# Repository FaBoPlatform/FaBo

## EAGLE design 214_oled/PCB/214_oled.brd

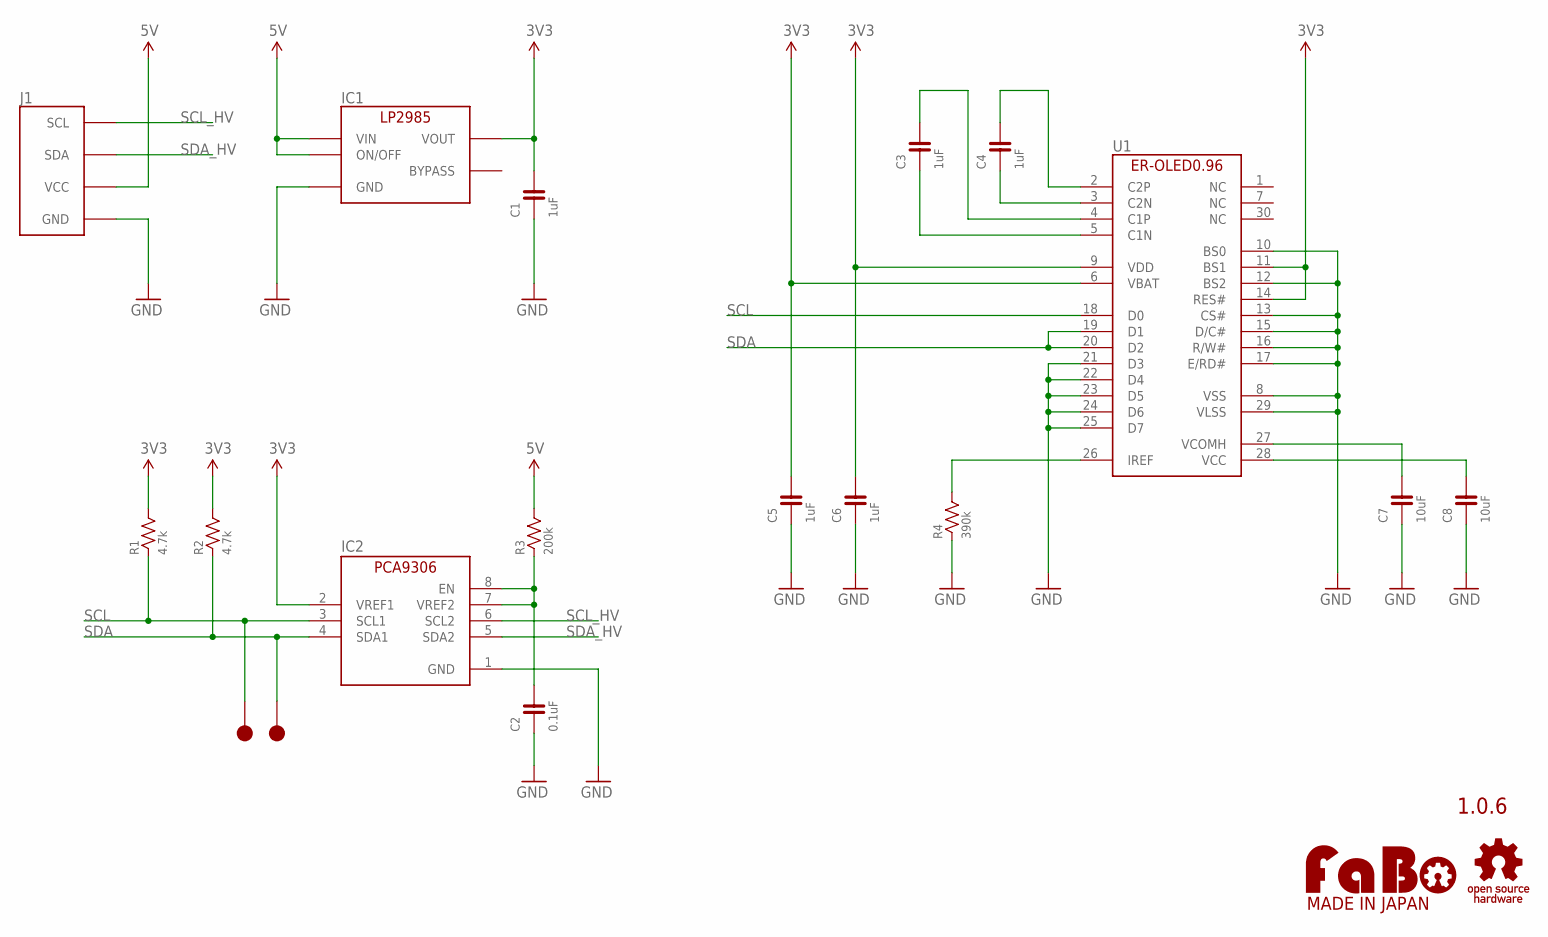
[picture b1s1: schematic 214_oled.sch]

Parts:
C1, C3, C4, C5, C6: 1uF; 0603
C2: 0.1uF; 0603
C7, C8: 10uF; 0603
IC1: LP2985-33DBV; SOT-23-5
IC2: PCA9306GM; XQFN8
J1: FABO_BRICK_I2C-OLED; FABO_BRICK_I2C_OLED
R1, R2: 4.7k; 0603
R3: 200k; 0603
R4: 390k; 0603
TP1, TP2: TP-15
U1: ER-OLED0.96-1
U$2: LOGO_OSHW-M; LOGO_OSHW_M
U$3: LOGO_FABO-M_BOTTOM; LOGO_FABO_MS_BOTTOM

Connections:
3V3: C1.2, C5.2, C6.2, IC1.5 (VOUT), IC2.2 (VREF1), R1.2, R2.2, U1.6 (VBAT), U1.9 (VDD), U1.11 (BS1), U1.14 (RES#)
5V: IC1.1 (VIN), IC1.3 (ON/OFF), J1.VCC, R3.2
GND: C1.1, C2.1, C5.1, C6.1, C7.1, C8.1, IC1.2 (GND), IC2.1 (GND), J1.GND, R4.1, U1.8 (VSS), U1.10 (BS0), U1.12 (BS2), U1.13 (CS#), U1.15 (D/C#), U1.16 (R/W#), U1.17 (E/RD#), U1.21 (D3), U1.22 (D4), U1.23 (D5), U1.24 (D6), U1.25 (D7), U1.29 (VLSS)
unnamed: C3.2, U1.4 (C1P)
unnamed: C3.1, U1.5 (C1N)
unnamed: C4.1, U1.3 (C2N)
unnamed: C4.2, U1.2 (C2P)
unnamed: R4.2, U1.26 (IREF)
unnamed: C7.2, U1.27 (VCOMH)
unnamed: C8.2, U1.28 (VCC)
unnamed: C2.2, IC2.7 (VREF2), IC2.8 (EN), R3.1
SCL: IC2.3 (SCL1), R1.1, TP2.1, U1.18 (D0)
SCL_HV: IC2.6 (SCL2), J1.SCL
SDA: IC2.4 (SDA1), R2.1, TP1.1, U1.19 (D1), U1.20 (D2)
SDA_HV: IC2.5 (SDA2), J1.SDA

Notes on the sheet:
1.0.6

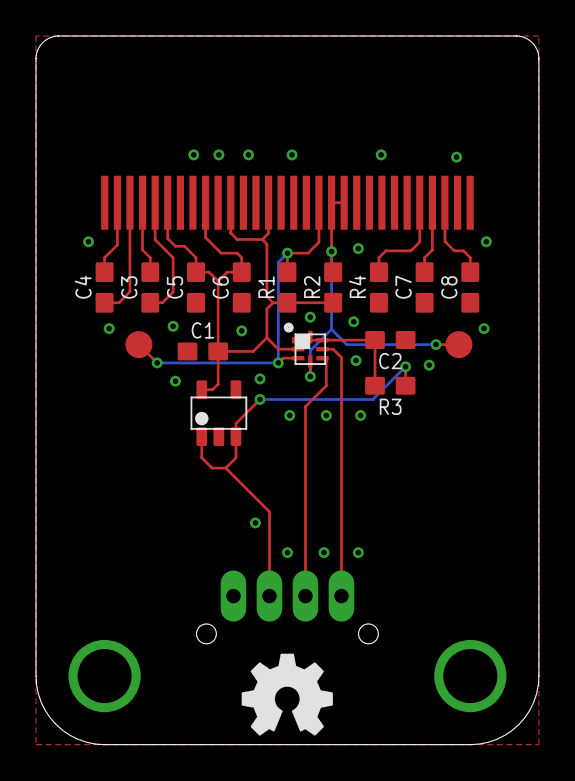
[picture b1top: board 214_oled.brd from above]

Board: 2 copper layers, 27.9 x 39.4 mm, 20 parts (1 on the bottom side), 15 nets.

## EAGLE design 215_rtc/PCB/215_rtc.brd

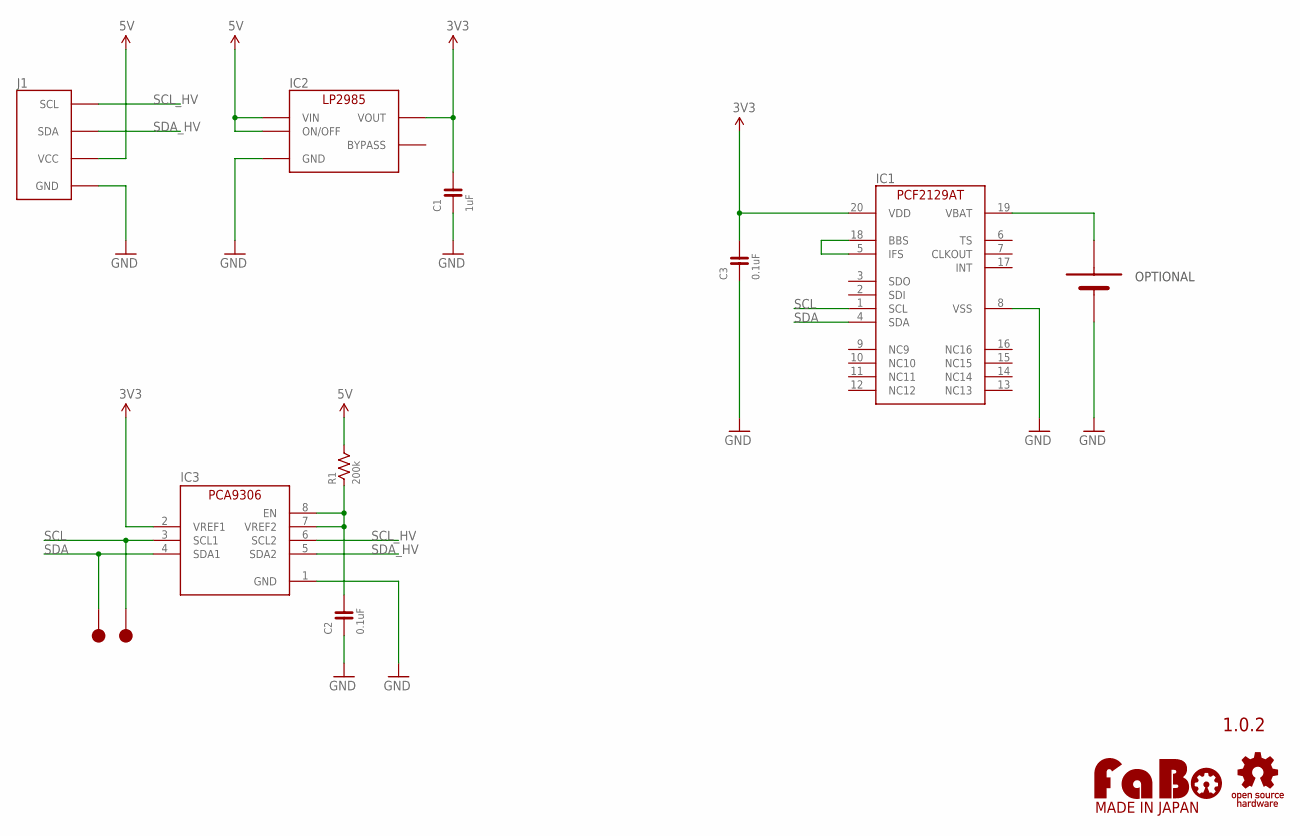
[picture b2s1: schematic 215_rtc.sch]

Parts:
C1: 1uF; 0603
C2, C3: 0.1uF; 0603
IC1: RTC-PCF2129AT; SO20
IC2: TI-LP2985-33DBVR; TI-LP2985
IC3: PCA9306DQER; X2SON
J1: FABO_BRICK_I2C
R1: 200k; 0603
TP1, TP2: TP-10
U$2: LOGO_OSHW-M_BOTTOM; LOGO_OSHW_M_BOTTOM
U$3: LOGO_FABO-M; LOGO_FABO_MS
U$4: BATTERY-SMTU2450; TAKACHI-SMTU2450

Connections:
3V3: C1.2, C3.2, IC1.20 (VDD), IC2.5 (VOUT), IC3.2 (VREF1)
5V: IC2.1 (VIN), IC2.3 (ON/OFF), J1.VCC, R1.2
GND: C1.1, C2.1, C3.1, IC1.8 (VSS), IC2.2 (GND), IC3.1 (GND), J1.GND, U$4.2 (-)
unnamed: IC1.19 (VBAT), U$4.1 (+)
unnamed: C2.2, IC3.7 (VREF2), IC3.8 (EN), R1.1
unnamed: IC1.5 (IFS), IC1.18 (BBS)
SCL: IC1.1 (SCL), IC3.3 (SCL1), TP2.1
SCL_HV: IC3.6 (SCL2), J1.SCL
SDA: IC1.4 (SDA), IC3.4 (SDA1), TP1.1
SDA_HV: IC3.5 (SDA2), J1.SDA

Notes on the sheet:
1.0.2
OPTIONAL

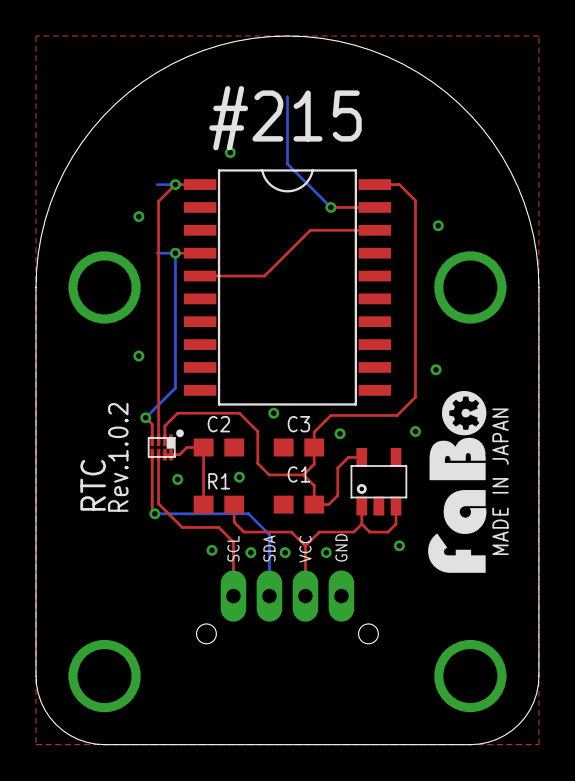
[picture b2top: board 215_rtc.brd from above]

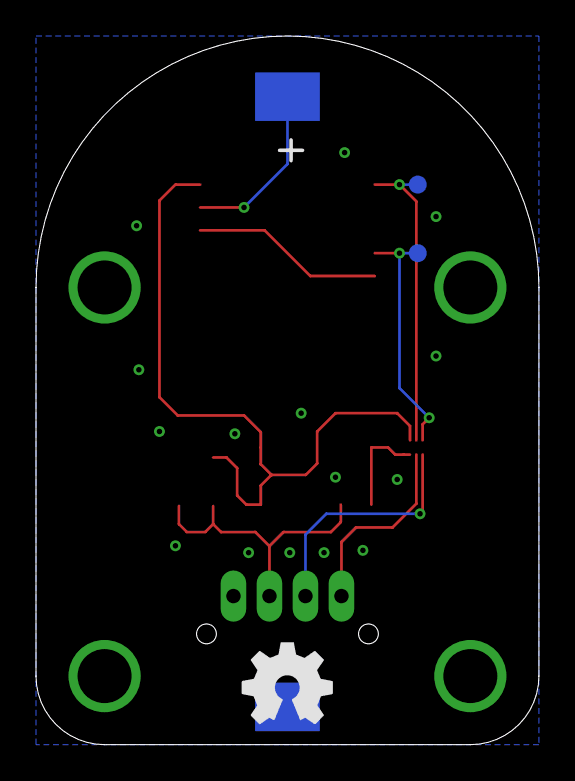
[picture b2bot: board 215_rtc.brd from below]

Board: 2 copper layers, 27.9 x 39.4 mm, 13 parts (3 on the bottom side), 10 nets.

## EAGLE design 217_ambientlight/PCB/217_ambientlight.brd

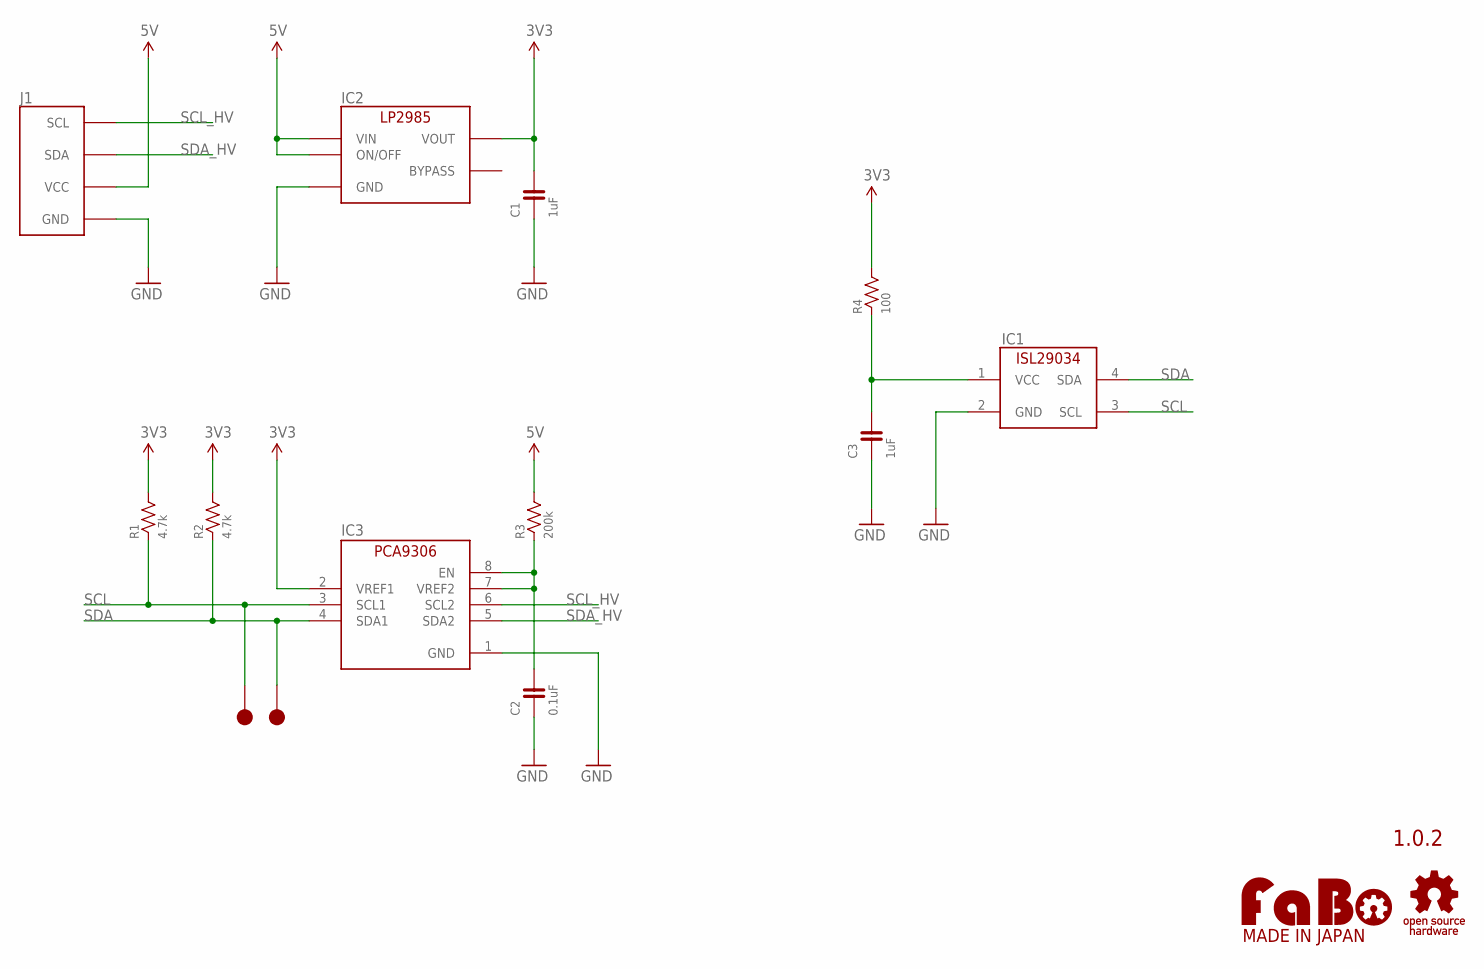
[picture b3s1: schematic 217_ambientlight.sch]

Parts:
C1, C3: 1uF; 0603
C2: 0.1uF; 0603
IC1: IN-ISL29034; INTERSIL-ISL29034
IC2: LP2985-33DBV; SOT-23-5
IC3: PCA9306GM; XQFN8
J1: FABO_BRICK_I2C
R1, R2: 4.7k; 0603
R3: 200k; 0603
R4: 100; 0603
TP1, TP2: TP-15
U$2: LOGO_OSHW-M_BOTTOM; LOGO_OSHW_M_BOTTOM
U$3: LOGO_FABO-M; LOGO_FABO_MS

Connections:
3V3: C1.2, IC2.5 (VOUT), IC3.2 (VREF1), R1.2, R2.2, R4.2
5V: IC2.1 (VIN), IC2.3 (ON/OFF), J1.VCC, R3.2
GND: C1.1, C2.1, C3.1, IC1.2 (GND), IC2.2 (GND), IC3.1 (GND), J1.GND
unnamed: C2.2, IC3.7 (VREF2), IC3.8 (EN), R3.1
SCL: IC1.3 (SCL), IC3.3 (SCL1), R1.1, TP2.1
SCL_HV: IC3.6 (SCL2), J1.SCL
SDA: IC1.4 (SDA), IC3.4 (SDA1), R2.1, TP1.1
SDA_HV: IC3.5 (SDA2), J1.SDA
VCC: C3.2, IC1.1 (VCC), R4.1

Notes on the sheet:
1.0.2

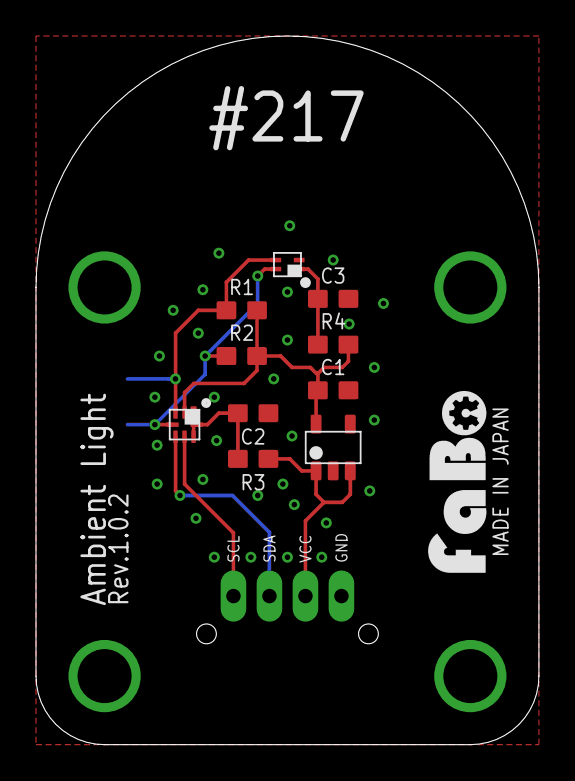
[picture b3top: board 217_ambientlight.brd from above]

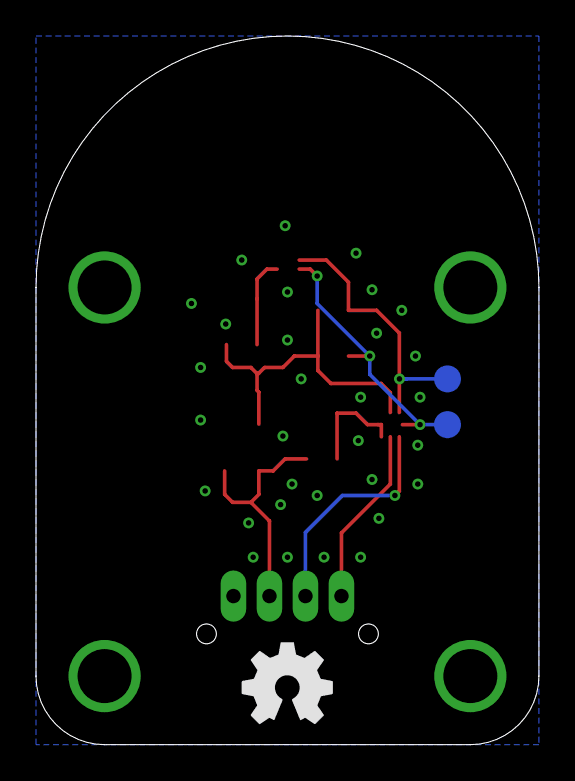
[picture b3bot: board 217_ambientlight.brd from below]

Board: 2 copper layers, 27.9 x 39.4 mm, 15 parts (2 on the bottom side), 9 nets.

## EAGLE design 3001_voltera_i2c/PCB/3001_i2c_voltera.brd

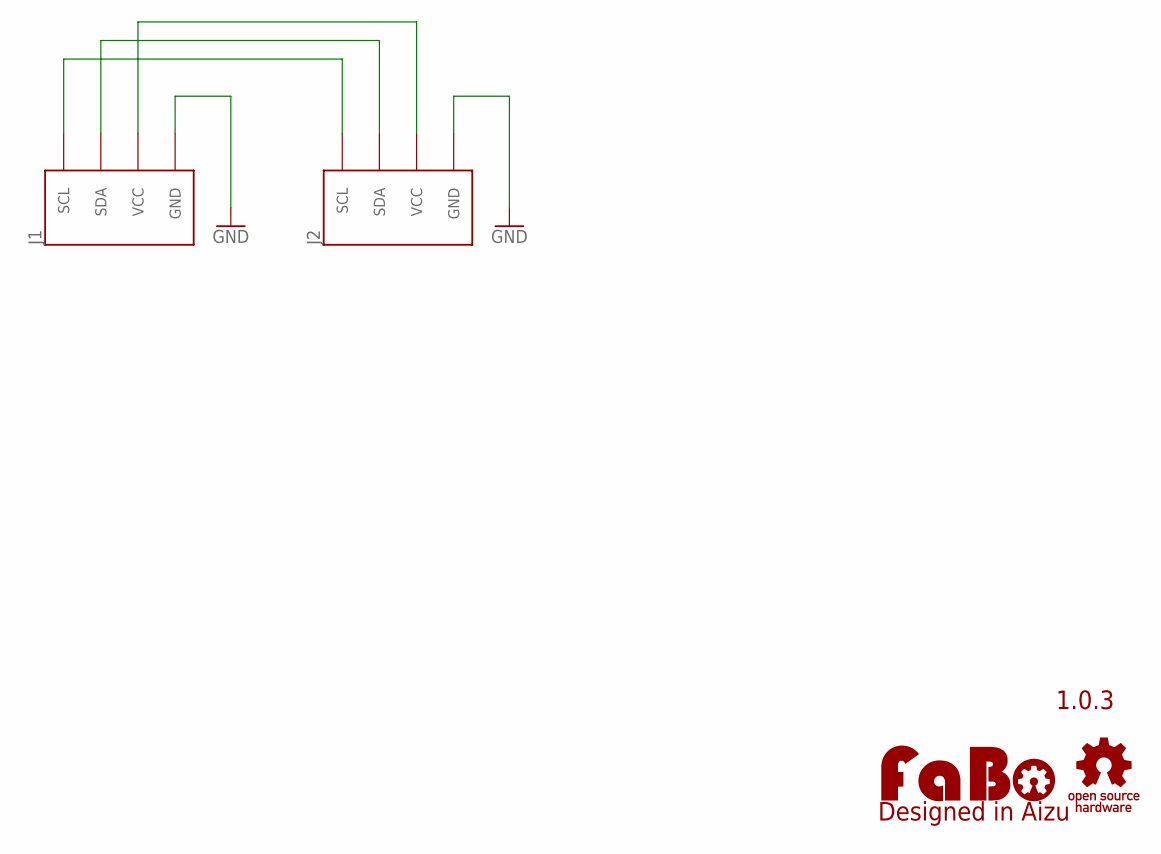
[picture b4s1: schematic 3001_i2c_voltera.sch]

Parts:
J1: FABO_BRICK_I2C-VOLTERA-BASE; FABO_BRICK_I2C_VOLTERA_BASE
J2: FABO_BRICK_I2C-VOLTERA-PAD; FABO_BRICK_I2C_VOLTERA_PAD
U$2: LOGO_OSHW-M_BOTTOM; LOGO_OSHW_M_BOTTOM
U$3: LOGO_FABO-S; LOGO_FABO_S

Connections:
GND: J1.GND, J2.GND
unnamed: J1.SCL, J2.SCL
unnamed: J1.SDA, J2.SDA
unnamed: J1.VCC, J2.VCC

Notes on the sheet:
1.0.3

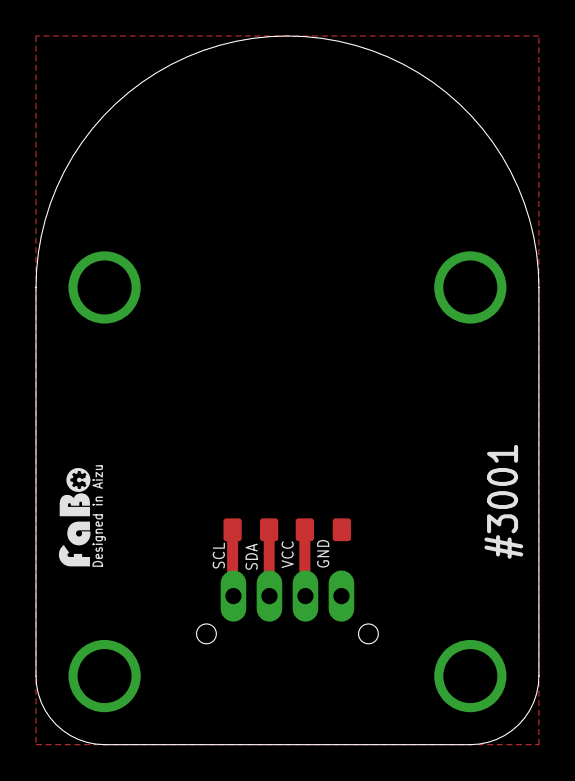
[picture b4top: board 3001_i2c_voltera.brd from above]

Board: 2 copper layers, 27.9 x 39.4 mm, 4 parts (0 on the bottom side), 4 nets.

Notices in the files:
parts and their libraries:
FaBo-etc: Released under the Creative Commons Attribution-ShareAlike 4.0 License
https://creativecommons.org/licenses/by-sa/4.0
FaBo-etc: Released under the Creative Commons
